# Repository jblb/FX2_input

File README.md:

FX2_input
=========

Input board for FX2 bazed logic analyser - to use with sigrok.org

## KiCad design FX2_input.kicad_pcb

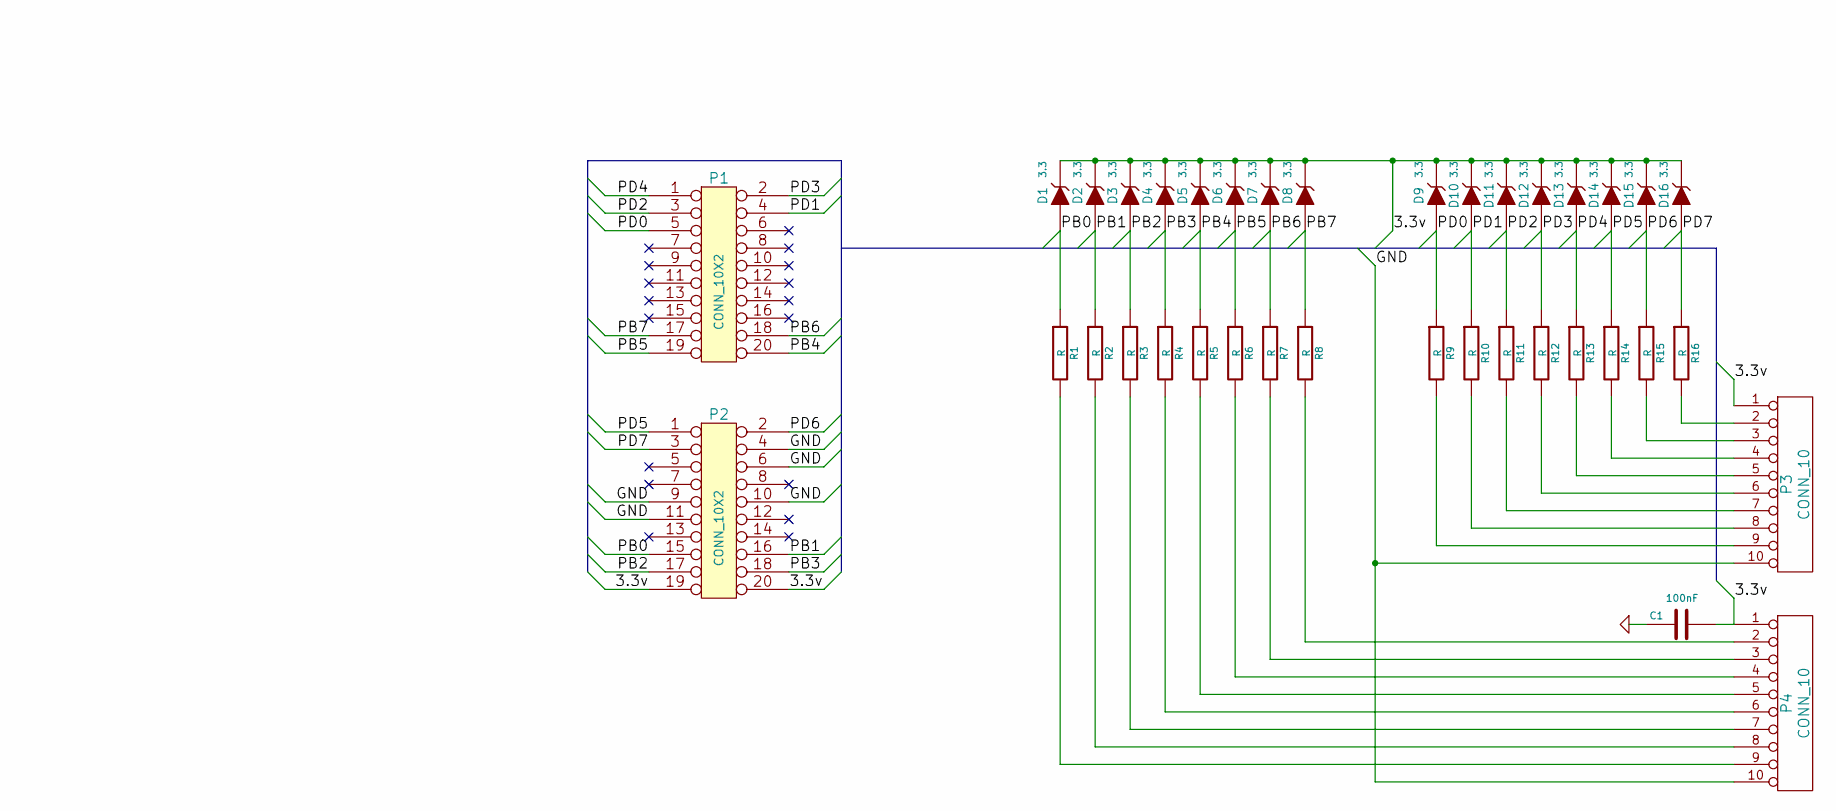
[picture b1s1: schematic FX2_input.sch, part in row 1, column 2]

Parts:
C1: 100nF
D1, D2, D3, D4, D5, D6, D7, D8, D9, D10, D11, D12, D13, D14, D15, D16: 3.3
P1, P2: CONN_10X2
P3, P4: CONN_10
R1, R2, R3, R4, R5, R6, R7, R8, R9, R10, R11, R12, R13, R14, R15, R16: R

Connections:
/3.3v: C1.2, D1.2 (K), D2.2 (K), D3.2 (K), D4.2 (K), D5.2 (K), D6.2 (K), D7.2 (K), D8.2 (K), D9.2 (K), D10.2 (K), D11.2 (K), D12.2 (K), D13.2 (K), D14.2 (K), D15.2 (K), D16.2 (K), P2.19, P2.20, P3.1, P4.1
/PB0: D1.1 (A), P2.15, R1.1
/PB1: D2.1 (A), P2.16, R2.1
/PB2: D3.1 (A), P2.17, R3.1
/PB3: D4.1 (A), P2.18, R4.1
/PB4: D5.1 (A), P1.20, R5.1
/PB5: D6.1 (A), P1.19, R6.1
/PB6: D7.1 (A), P1.18, R7.1
/PB7: D8.1 (A), P1.17, R8.1
/PD0: D9.1 (A), P1.5, R9.1
/PD1: D10.1 (A), P1.4, R10.1
/PD2: D11.1 (A), P1.3, R11.1
/PD3: D12.1 (A), P1.2, R12.1
/PD4: D13.1 (A), P1.1, R13.1
/PD5: D14.1 (A), P2.1, R14.1
/PD6: D15.1 (A), P2.2, R15.1
/PD7: D16.1 (A), P2.3, R16.1
GND: C1.1, P2.4, P2.6, P2.9, P2.10, P2.11, P3.10, P4.10
unnamed: P4.9, R1.2
unnamed: P3.5, R13.2
unnamed: P4.3, R7.2
unnamed: P3.7, R11.2
unnamed: P3.4, R14.2
unnamed: P3.3, R15.2
unnamed: P4.6, R4.2
unnamed: P4.5, R5.2
unnamed: P3.9, R9.2
unnamed: P4.2, R8.2
unnamed: P4.4, R6.2
unnamed: P4.7, R3.2
unnamed: P4.8, R2.2
unnamed: P3.2, R16.2
unnamed: P3.6, R12.2
unnamed: P3.8, R10.2

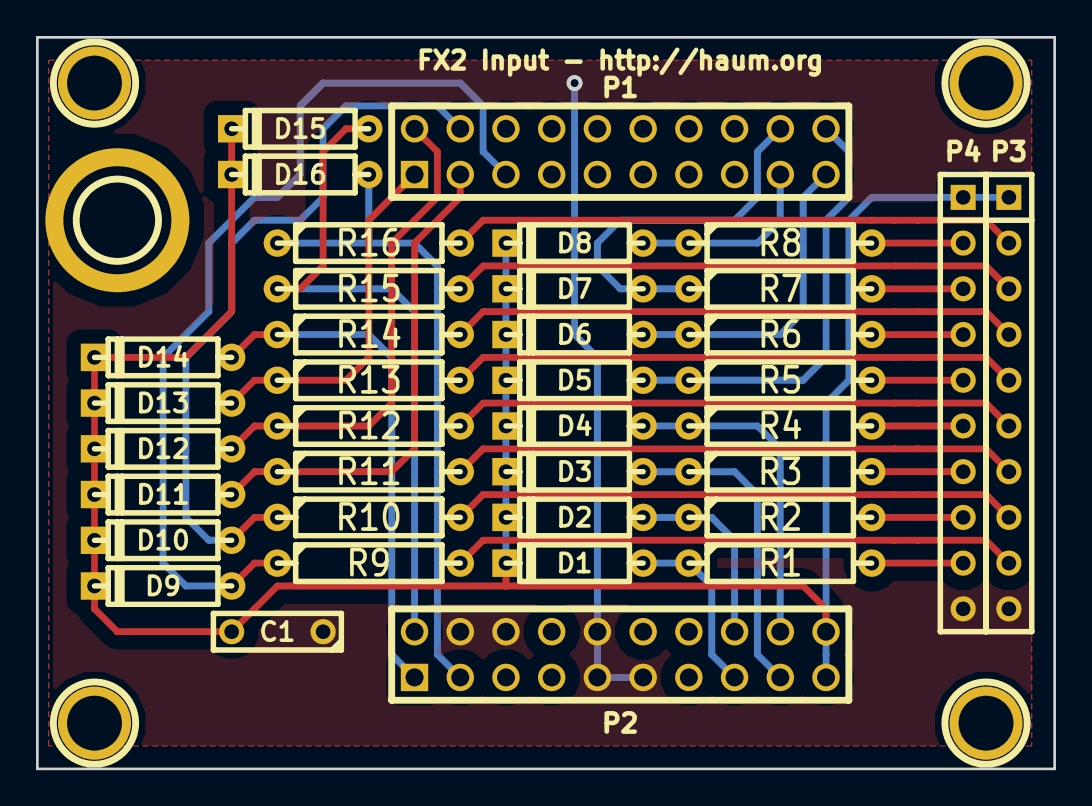
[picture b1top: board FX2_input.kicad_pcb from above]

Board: 2 copper layers, 56.5 x 40.6 mm, 42 parts (0 on the bottom side), 34 nets.

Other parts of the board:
1PIN, 1PIN#2, 1PIN#3, 1PIN#4, 1PIN#5: P***; 1pin

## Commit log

2014-02-13 ajout alim sur connecteur de mesure - ajout decouplage
2014-02-13 redessin carte et positionnement fixation - inter (WIP)
2014-02-14 new version - fit base board & power on connector
2014-02-17 ajustement percages
2014-02-17 ajustement percages - encore
2014-02-21 ajustement gitignore
